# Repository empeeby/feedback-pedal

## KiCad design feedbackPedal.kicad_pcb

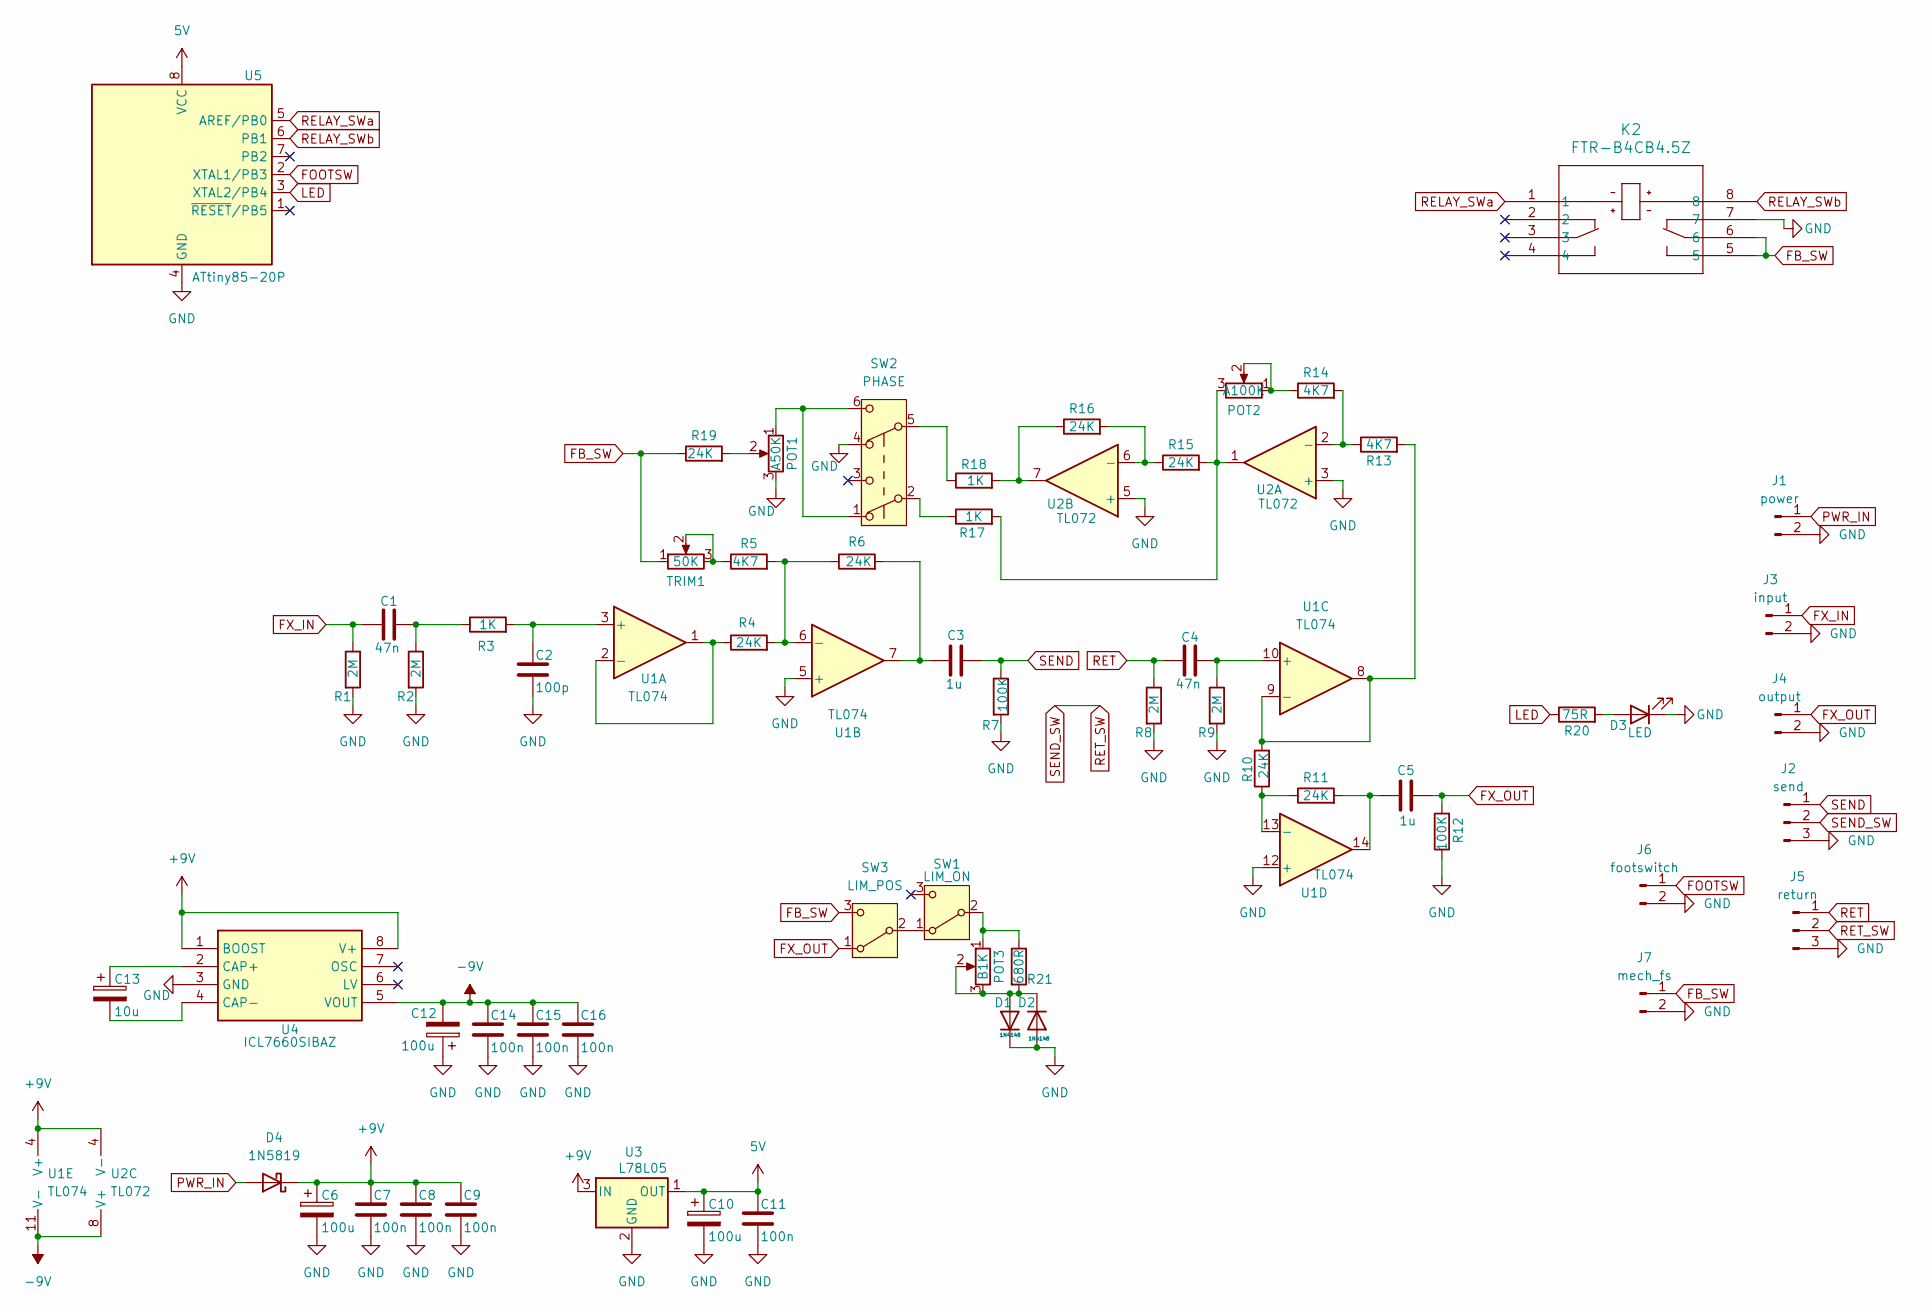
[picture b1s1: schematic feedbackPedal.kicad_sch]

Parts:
C1, C4: 47n; C_0603_1608Metric
C2: 100p; C_0603_1608Metric
C3, C5: 1u; C_0603_1608Metric
C6, C10, C12: 100u; CP_Elec_5x5.4
C7, C8, C9, C11, C14, C15, C16: 100n; C_0603_1608Metric
C13: 10u; CP_Elec_5x5.4
D1, D2: 1N4148; D_SOD-123
D3: LED; LED_D3.0mm
D4: 1N5819; D_SOD-323
J1: power; PinHeader_1x02_P2.54mm_Vertical
J2: send; PinHeader_1x03_P2.54mm_Vertical
J3: input; PinHeader_1x02_P2.54mm_Vertical
J4: output; PinHeader_1x02_P2.54mm_Vertical
J5: return; PinHeader_1x03_P2.54mm_Vertical
J6: footswitch; PinHeader_1x02_P2.54mm_Vertical
J7: mech_fs; PinHeader_1x02_P2.54mm_Vertical
K2: FTR-B4CB4.5Z; FTR-B4C_FUJ
POT1: A50K; Potentiometer_Alpha_RD901F-40-00D_Single_Vertical_CENTREMARK
POT2: A100K; Potentiometer_Alpha_RD901F-40-00D_Single_Vertical_CENTREMARK
POT3: B1K; Potentiometer_Alpha_RD901F-40-00D_Single_Vertical_CENTREMARK
R1, R2, R8, R9: 2M; R_0603_1608Metric
R3, R17, R18: 1K; R_0603_1608Metric
R4, R6, R10, R11, R15, R16, R19: 24K; R_0603_1608Metric
R5, R13, R14: 4K7; R_0603_1608Metric
R7, R12: 100K; R_0603_1608Metric
R20: 75R; R_0603_1608Metric
R21: 680R; R_Axial_DIN0204_L3.6mm_D1.6mm_P5.08mm_Horizontal
SW1: LIM_ON; 2MS1T1-M2_DYW
SW2: PHASE; 2MD1T1B1M2QES-5
SW3: LIM_POS; SS-12D10G5_XKB
TRIM1: 50K; Potentiometer_Bourns_3296W_Vertical
U1: TL074; SOIC-14_3.9x8.7mm_P1.27mm
U2: TL072; SOIC-8_3.9x4.9mm_P1.27mm
U3: L78L05; SOT-89-3
U4: ICL7660SIBAZ; SOIC-8_3.9x4.9mm_P1.27mm; Mouser Part Number 968-ICL7660SIBAZ
U5: ATtiny85-20P; DIP-8_W7.62mm

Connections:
5V: C10.1, C11.1, U3.1 (OUT), U5.8 (VCC)
+9V: C6.1, C7.1, C8.1, C9.1, D4.1 (K), U1.4 (V+), U2.4 (V-), U3.3 (IN), U4.1 (BOOST), U4.8 (V+)
-9V: C12.2, C14.1, C15.1, C16.1, U1.11 (V-), U2.8 (V+), U4.5 (VOUT)
FB_SW: J7.1, K2.5, K2.6, R19.1, SW3.3 (C), TRIM1.1
FOOTSW: J6.1, U5.2 (XTAL1/PB3)
FX_IN: C1.1, J3.1, R1.1
FX_OUT: C5.2, J4.1, R12.2, SW3.1 (A)
GND: C2.2, C6.2, C7.2, C8.2, C9.2, C10.2, C11.2, C12.1, C14.2, C15.2, C16.2, D1.1 (K), D2.2 (A), D3.1 (K), J1.2, J2.3, J3.2, J4.2, J5.3, J6.2, J7.2, K2.7, POT1.3, R1.2, R2.2, R7.2, R8.2, R9.2, R12.1, SW2.4 (A), U1.5 (+), U1.12 (+), U2.3 (+), U2.5 (+), U3.2 (GND), U4.3 (GND), U5.4 (GND)
LED: R20.1, U5.3 (XTAL2/PB4)
unnamed: C1.2, R2.1, R3.1
unnamed: C3.1, R6.2, U1.7
unnamed: C5.1, R11.2, U1.14
unnamed: D1.2 (A), D2.1 (K), POT3.2, POT3.3, R21.2
unnamed: D3.2 (A), R20.2
unnamed: POT1.1, SW2.1 (A), SW2.6 (C)
unnamed: POT1.2, R19.2
unnamed: POT2.1, POT2.2, R14.1
unnamed: POT2.3, R15.2, R17.2, U2.1
unnamed: R5.1, TRIM1.2, TRIM1.3
unnamed: R16.1, R18.2, U2.7
unnamed: R17.1, SW2.2 (B)
unnamed: R18.1, SW2.5 (B)
unnamed: SW1.1 (A), SW3.2 (B)
unnamed: POT3.1, R21.1, SW1.2 (B)
unnamed: C2.1, R3.2, U1.3 (+)
unnamed: R4.1, U1.1, U1.2 (-)
unnamed: R4.2, R5.2, R6.1, U1.6 (-)
unnamed: C4.2, R9.1, U1.10 (+)
unnamed: R10.2, R13.2, U1.8, U1.9 (-)
unnamed: R10.1, R11.1, U1.13 (-)
unnamed: R13.1, R14.2, U2.2 (-)
unnamed: R15.1, R16.2, U2.6 (-)
unnamed: C13.1, U4.2 (CAP+)
unnamed: C13.2, U4.4 (CAP-)
PWR_IN: D4.2 (A), J1.1
RELAY_SWa: K2.1, U5.5 (AREF/PB0)
RELAY_SWb: K2.8, U5.6 (PB1)
RET: C4.1, J5.1, R8.1
RET_SW: J2.2, J5.2
SEND: C3.2, J2.1, R7.1

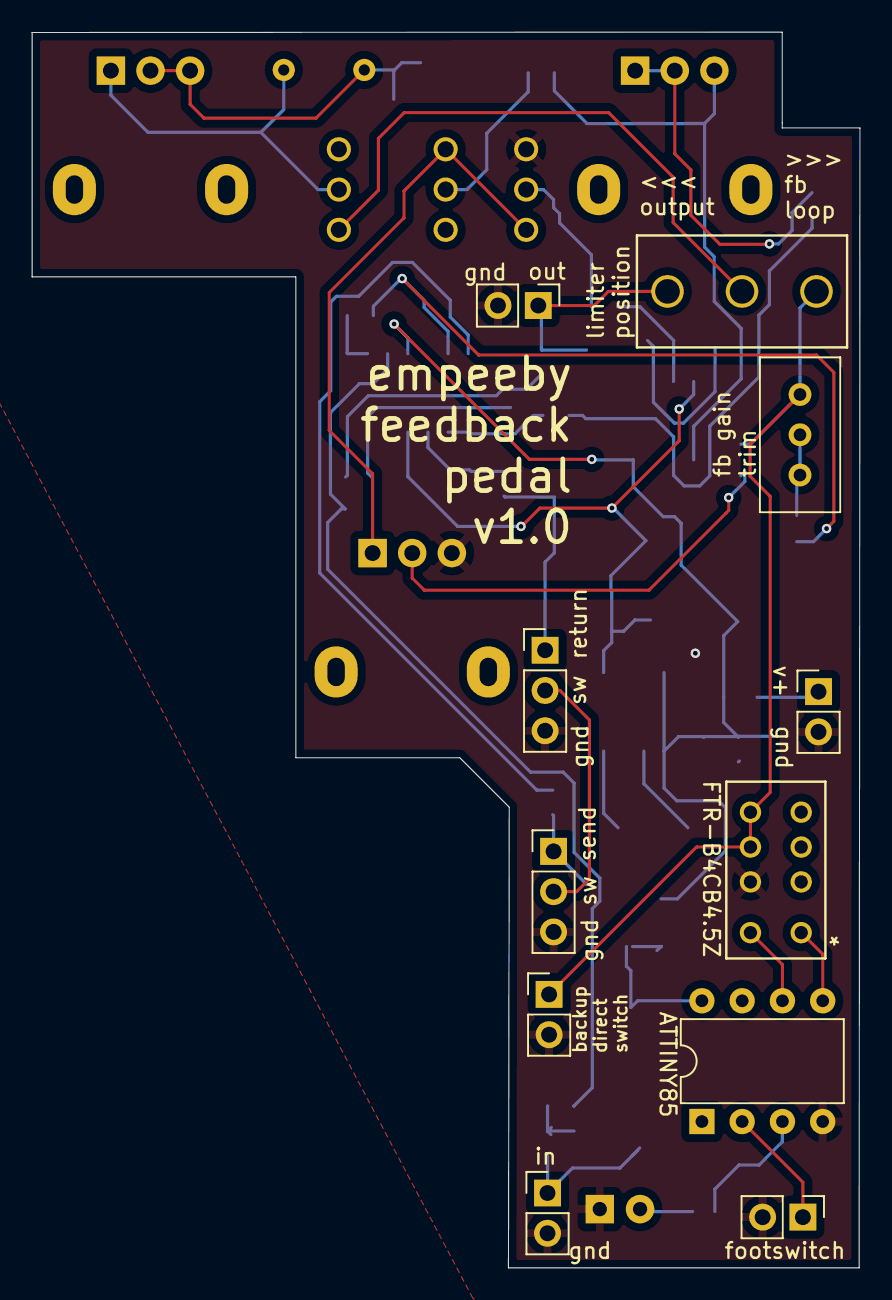
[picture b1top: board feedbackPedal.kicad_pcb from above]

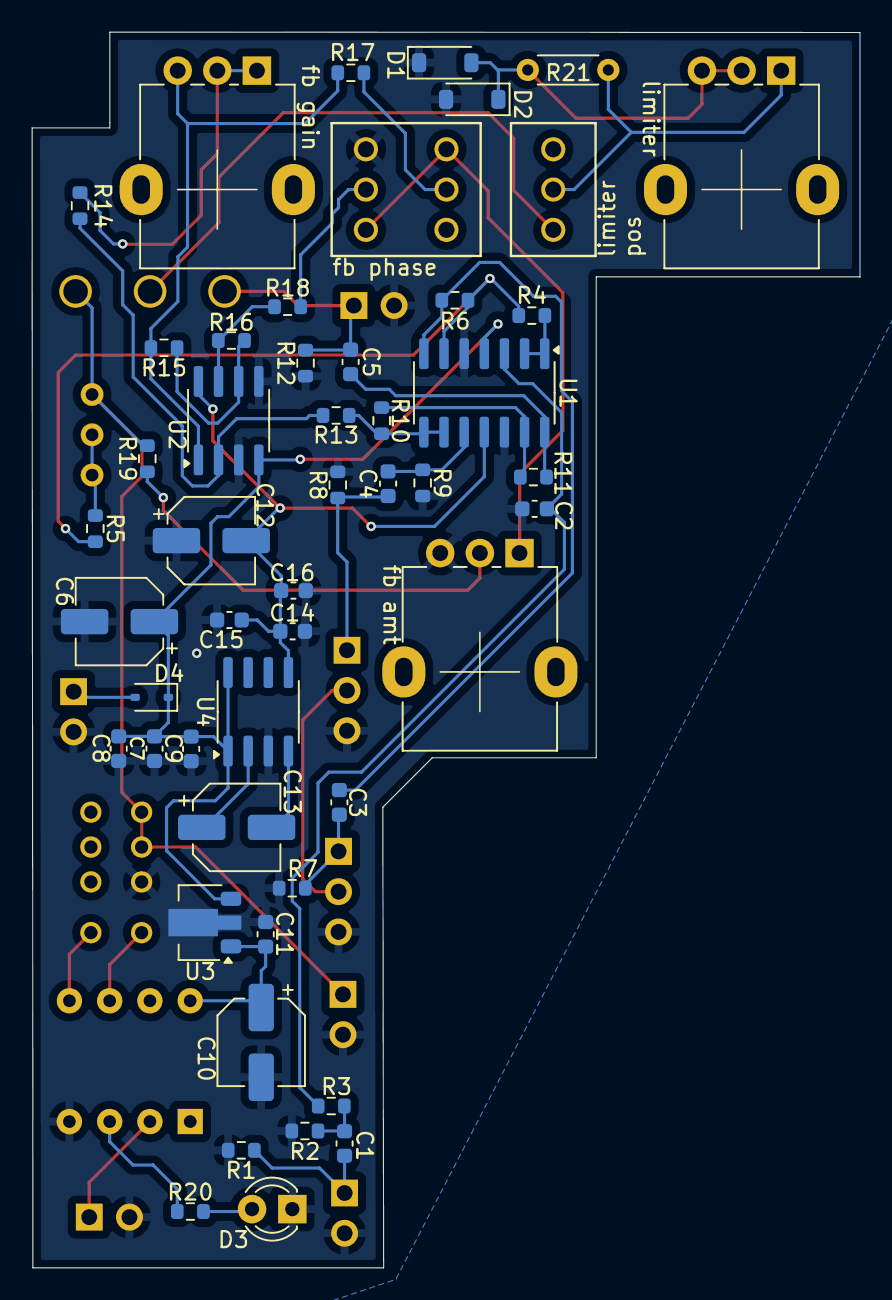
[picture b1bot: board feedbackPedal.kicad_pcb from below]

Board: 2 copper layers, 52.2 x 78.0 mm, 61 parts (50 on the bottom side), 40 nets.

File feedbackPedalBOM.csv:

Comment,Designator,Footprint,LCSC Part Number
47n,"C1,C4",0603,C1622
100p,C2,0603,C14858
1u,"C3,C5",0603,C15849
100u,"C6,C10,C12",5x5.4,C22469986
100n,"C7,C8,C9,C11,C14,C15,C16",0603,C14663
10u,C13,5x5.4,C189262
1N4148,"D1,D2",SOD-123,C81598
1N5819,D4,SOD-323,C191023
2M,"R1,R2,R8,R9",0603,C326730
1K,"R3,R17,R18",0603,C110776
24K,"R4,R6,R10,R11,R15,R16,R19",0603,C326729
4K7,"R5,R13,R14",0603,C513565
100K,"R7,R12",0603,C122538
75R,R20,0603,C4275
TL074,U1,SOIC-14,C12594
TL072,U2,SOIC-8,C6961
L78L05,U3,SOT-89-3,C42738
ICL7660SIBAZ,U4,SOIC-8,C7535
,,,
,,,
,,,
,,,
,,,
,,,
,,,
,,,
,,,
,,,
,,,
,,,
,,,
,,,
,,,
,,,
,,,
,,,

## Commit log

2025-10-26 init repo (first version already done)
2026-04-06 made some attiny tweaks
2026-05-29 add lockfiles to gitignore
2026-05-29 add archive dir
2026-05-29 create rough drill guide
2026-05-29 add claude history to gitignore
2026-05-29 replace attiny & relay with ch32 and analogue switch
2026-05-29 clear out autorecovered doc
